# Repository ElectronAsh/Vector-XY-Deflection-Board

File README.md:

# Vector-XY-Deflection-Board
XY Deflection Driver board for Vector arcade games

This is in Eagle format. I'm using Autodesk Eagle 9.0.1 atm.

Please note, this design is UNTESTED.
Please do NOT use the included Gerbers zip file yet. That was just for previewing the design.

There is also no output connector from the Spot Killer circuit added yet.

Originally based on this desgin...
http://www.e-basteln.de/arcade/asteroids/monitor/#improved-xy-deflection

I re-did the whole PCB layout, based on a 2-layer design.
(the original design was meant for single-layer, with a few wire links on the top side.)

I added a bridge rectifier to the board, and larger caps, so a centre-tapped transformer can be used directly.

The old fuses were removed, because fuse holders could (should?) be added externally to the transformer primary and secondaries.
(also might be easier to access external fuse holders instead of being directly on the board.)

(the deflection board uses sense resistors for the yoke current, and uses that as feedback to the opamp.
 It should be possible to add some current-limiting to the design later.
 I think a couple of external fuses on the transformer secondaries will offer half-decent protection in mean time.)

Plus I added the Gain pots, linearity pots, Spot Killer circuit, and larger main transistors + driver transistors, all based on this video series...
https://youtu.be/xNVZ1HK8R1w?t=1326

The larger transistors and driver transistors are now meant to be bolted to a heatsink, with the whole PCB mounted just above that.
Hence the holes in the PCB to allow access to the mounting screws for the transistors.

(The transistors can't easily be mounted to a heatsink at 90-degrees to the board any more, as the transistors would need to be flipped around.)

I think mounting them on a heatsink below the PCB will be a lot neater and more stable.
I guess a heatsink at 90-degrees to the board could still be used, but the transistors would need to point downwards from the underside of the PCB.

The "Unblank" RCA jack output was removed, which was originally intended for driving the Blanking input on the Vectrex power board.
The Unblank signal was pretty much just a resistor from the X yoke anyway, which was probably fine for the Vectrex, but didn't take into account the Y signal.

The new Spot Killer circuit does take into account both the X and Y signal inputs.
Once the output connector for that circuit is added, it will be able to blank the external Cathode (or RGB) driver if the Spot Killer circuit sees 
no deflection on either the X or Y input for a specific amount of time.

(that time-constant can be set by resistor/cap values in the Spot Killer circuit. A pot could be added later, to make that variable.)

I will try to get some PCBs ordered for this soon, to test it.

The LT1227 opamps have a maximum supply rail voltage of +/- 18V.
A typical centre-tapped transformer with an output voltage of "12VRMS" (AC) will give a DC voltage of roughly 15V to 17V after the bridge rectifier.

So I would NOT recommending using a higher transformer voltage than that atm.
Maybe some shunt regulators could be added to the opamps?

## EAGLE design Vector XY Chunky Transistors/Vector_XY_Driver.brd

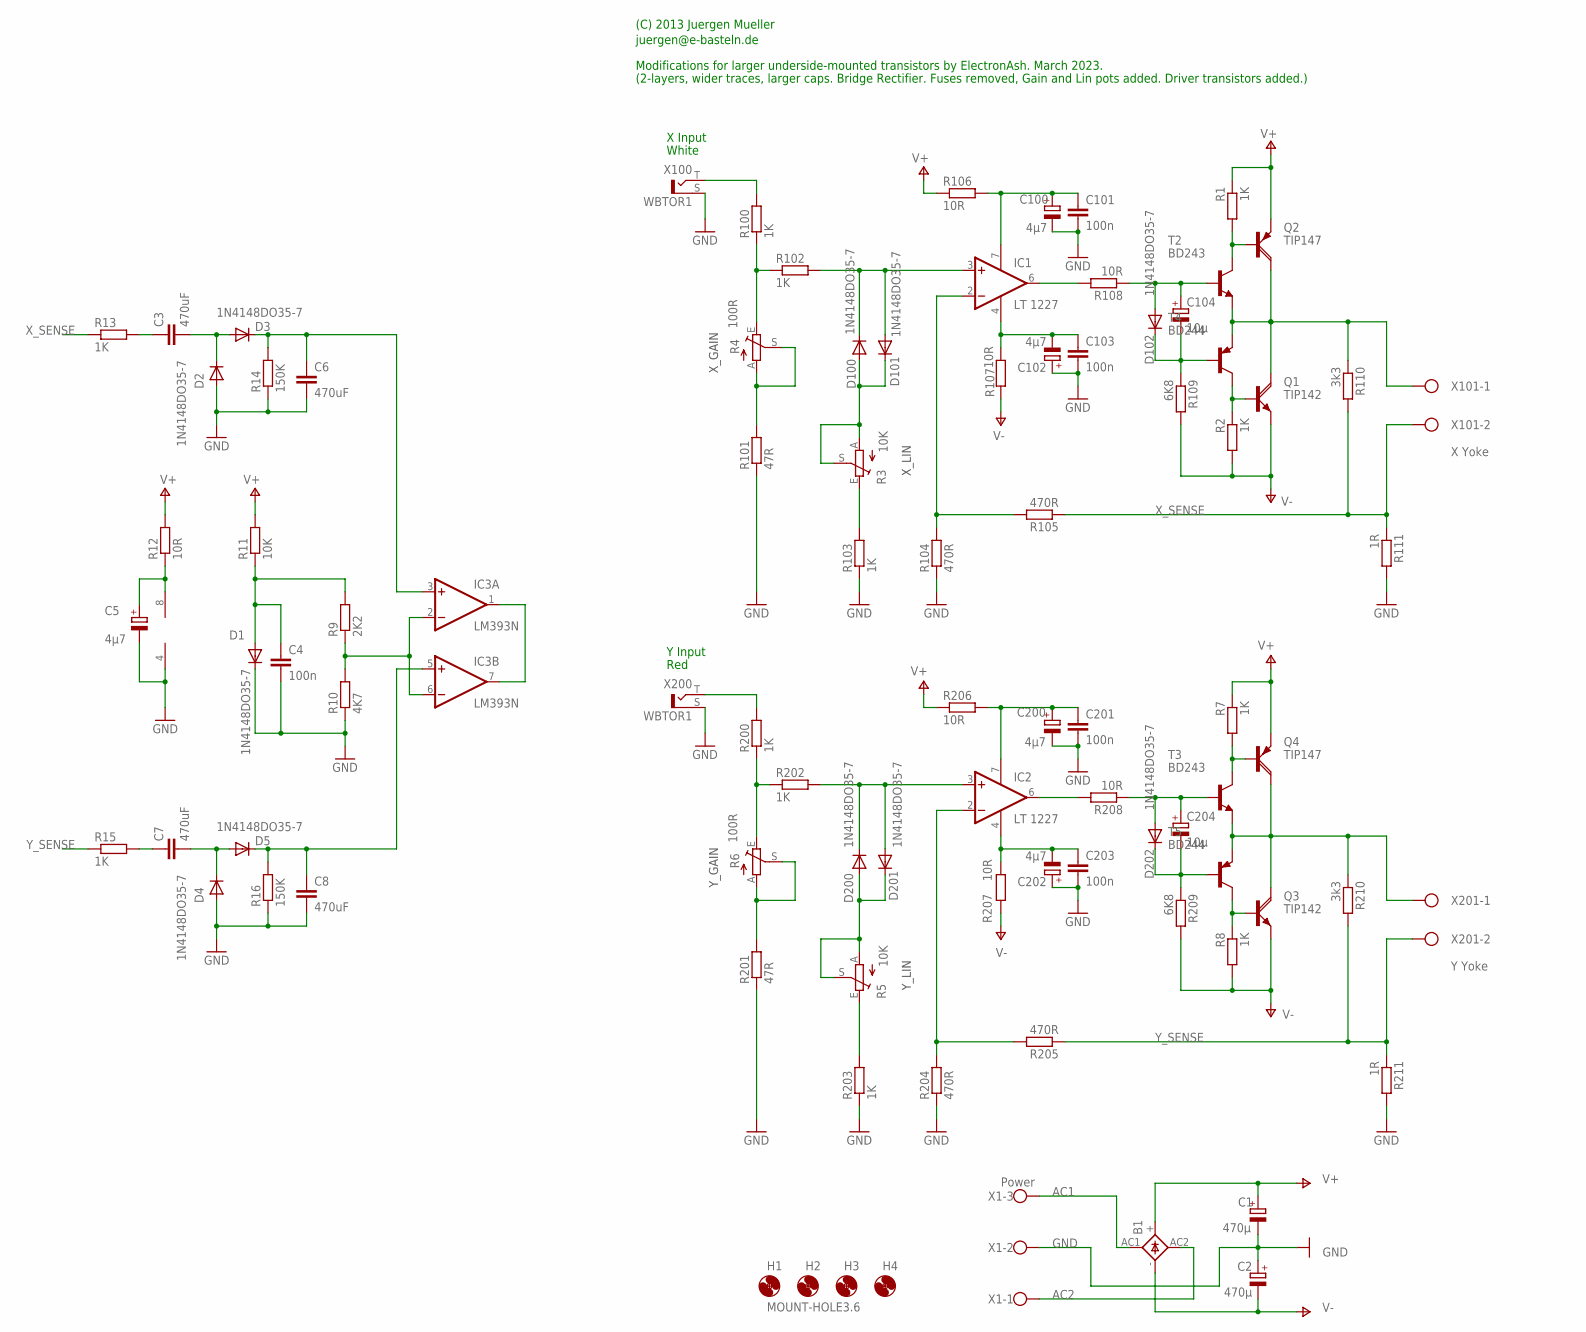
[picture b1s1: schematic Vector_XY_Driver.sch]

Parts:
B1: 2KBP
C1, C2: 470µ; E7,5-16
C3, C6, C7, C8: 470uF; C025_050-025X075
C4, C101, C103, C201, C203: 100n; C025_050-025X075
C5, C100, C102, C200, C202: 4µ7; E2,5-6
C104, C204: 10µ; E15-5
D1, D2, D3, D4, D5, D100, D101, D102, D200, D201, D202: 1N4148DO35-7; DO35-7
H1, H2, H3, H4: MOUNT-HOLE3.6; 3,6
IC1, IC2: LT 1227; DIL08
IC3: LM393N; DIL08
Q1, Q3: TIP142; SOT93
Q2, Q4: TIP147; SOT93
R1, R2, R7, R8, R13, R15, R100, R102, R103, R200, R202, R203: 1K; 0207/10
R3, R5: 10K; B25P
R4, R6: 100R; B25P
R9: 2K2; 0207/10
R10: 4K7; 0207/10
R11: 10K; 0207/10
R12: 10R; 0207/10
R14, R16: 150K; 0207/10
R101, R201: 47R; 0207/10
R104, R105, R204, R205: 470R; 0207/10
R106, R107, R108, R206, R207, R208: 10R; 0207/12
R109, R209: 6K8; 0207/10
R110, R210: 3k3; 0207/10
R111, R211: 1R; 0617/17
T2, T3: BD243; TO220
T4, T5: BD244; TO220
X1: Power; W237-103
X100, X200: WBTOR1
X101: X Yoke; W237-102
X201: Y Yoke; W237-102

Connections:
AC1: B1.AC1, X1.3
AC2: B1.AC2, X1.1
GND: C1.-, C2.+, C4.2, C5.-, C6.2, C8.2, C100.-, C101.2, C102.+, C103.2, C200.-, C201.2, C202.+, C203.2, D1.C, D2.A, D4.A, IC3.4 (V-), R10.1, R14.1, R16.1, R101.1, R103.1, R104.1, R111.2, R201.1, R203.1, R204.1, R211.2, X1.2, X100.S, X200.S
unnamed: C102.-, C103.1, IC1.4 (V-), R107.1
unnamed: C100.+, C101.1, IC1.7 (V+), R106.2
unnamed: IC1.2 (-IN), R104.2, R105.2
unnamed: R3.E, R103.2
unnamed: IC1.6 (OUT), R108.2
unnamed: C104.+, D102.A, R108.1, T2.1 (B)
unnamed: C104.-, D102.C, R109.1, T4.1 (B)
unnamed: Q2.B, R1.2, T2.2 (C)
unnamed: D100.A, D101.C, R3.A, R3.S
unnamed: R5.E, R203.2
unnamed: IC3.1 (OUT), IC3.7 (OUT)
unnamed: D100.C, D101.A, IC1.3 (+IN), R102.2
unnamed: R4.E, R100.1, R102.1
unnamed: R100.2, X100.T
unnamed: C202.-, C203.1, IC2.4 (V-), R207.1
unnamed: C200.+, C201.1, IC2.7 (V+), R206.2
unnamed: IC2.6 (OUT), R208.2
unnamed: C204.+, D202.A, R208.1, T3.1 (B)
unnamed: C204.-, D202.C, R209.1, T5.1 (B)
unnamed: Q3.C, Q4.C, R210.1, T3.3 (E), T5.3 (E), X201.1
unnamed: Q1.C, Q2.C, R110.1, T2.3 (E), T4.3 (E), X101.1
unnamed: Q1.B, R2.1, T4.2 (C)
unnamed: IC2.2 (-IN), R204.2, R205.2
unnamed: C5.+, IC3.8 (V+), R12.1
unnamed: D200.C, D201.A, IC2.3 (+IN), R202.2
unnamed: R6.E, R200.1, R202.1
unnamed: R200.2, X200.T
unnamed: R4.A, R4.S, R101.2
unnamed: R6.A, R6.S, R201.2
unnamed: D200.A, D201.C, R5.A, R5.S
unnamed: Q3.B, R8.1, T5.2 (C)
unnamed: Q4.B, R7.2, T3.2 (C)
unnamed: IC3.2 (-IN), IC3.6 (-IN), R9.1, R10.2
unnamed: C4.1, D1.A, R9.2, R11.1
unnamed: C6.1, D3.C, IC3.3 (+IN), R14.2
unnamed: C3.2, D2.C, D3.A
unnamed: C3.1, R13.2
unnamed: C8.1, D5.C, IC3.5 (+IN), R16.2
unnamed: C7.2, D4.C, D5.A
unnamed: C7.1, R15.2
V+: B1.+, C1.+, Q2.E, Q4.E, R1.1, R7.1, R11.2, R12.2, R106.1, R206.1
V-: B1.-, C2.-, Q1.E, Q3.E, R2.2, R8.2, R107.2, R109.2, R207.2, R209.2
X_SENSE: R13.1, R105.1, R110.2, R111.1, X101.2
Y_SENSE: R15.1, R205.1, R210.2, R211.1, X201.2

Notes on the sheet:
X Input
Y Input
White
Red
(C) 2013 Juergen Mueller
juergen@e-basteln.de
Modifications for larger underside-mounted transistors by ElectronAsh. March 2023.
(2-layers, wider traces, larger caps. Bridge Rectifier. Fuses removed, Gain and Lin pots added. Driver transistors added.)
X_LIN
X_GAIN
Y_GAIN
Y_LIN

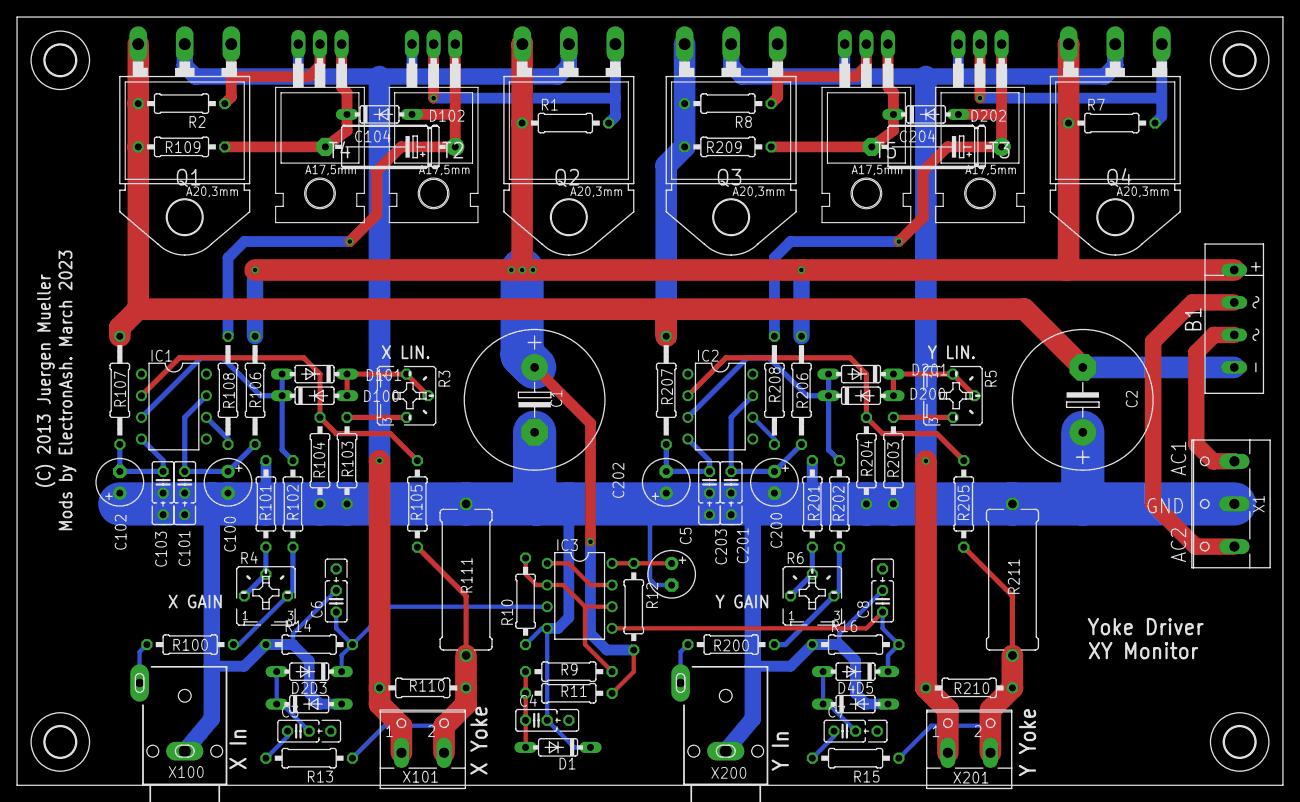
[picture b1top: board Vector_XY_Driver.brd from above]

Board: 2 copper layers, 148.6 x 90.2 mm, 90 parts (0 on the bottom side), 47 nets.

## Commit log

2023-03-09 Moved Eagle files into root folder, to make it easier to clone into a folder in Eagle projects
2023-03-09 Re-Added Eagle files
2023-03-09 Added images folder, and Eagle PCB screenshot
